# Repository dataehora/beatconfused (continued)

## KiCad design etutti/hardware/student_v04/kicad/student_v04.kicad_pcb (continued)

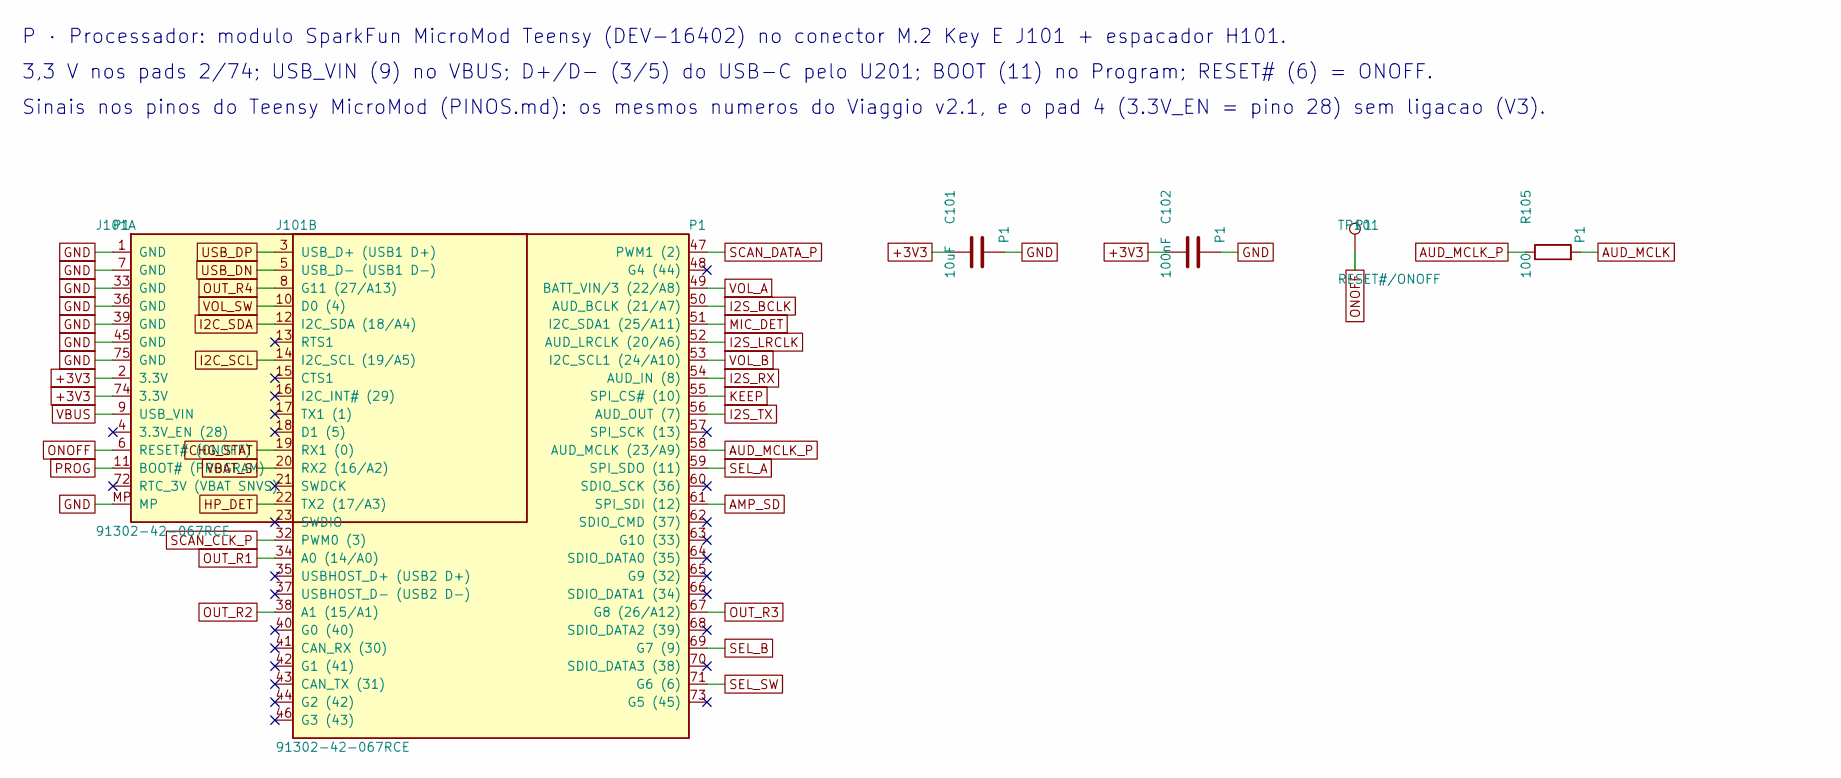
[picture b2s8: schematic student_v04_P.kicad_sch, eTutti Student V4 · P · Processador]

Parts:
C101: 10uF; C_0805_2012Metric; LCSC C15850
C102: 100nF; C_0402_1005Metric; LCSC C1525
J101: 91302-42-067RCE; M.2_E_H4.2_UMAX_91302-42-067; LCSC C48985906
R105: 100; R_0402_1005Metric; LCSC C25076
TP101: RESET#/ONOFF; TestPoint_Pad_D1.5mm

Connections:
+3V3: C101.1, C102.1, J101.2 (3.3V), J101.74 (3.3V); also elsewhere on the board
AMP_SD: J101.61 (SPI_SDI (12)); also elsewhere on the board
AUD_MCLK: R105.2; also elsewhere on the board
AUD_MCLK_P: J101.58 (AUD_MCLK (23/A9)), R105.1
CHG_STAT: J101.19 (RX1 (0)); also elsewhere on the board
GND: C101.2, C102.2, J101.1 (GND), J101.7 (GND), J101.33 (GND), J101.36 (GND), J101.39 (GND), J101.45 (GND), J101.75 (GND), J101.MP; also elsewhere on the board
HP_DET: J101.22 (TX2 (17/A3)); also elsewhere on the board
I2C_SCL: J101.14 (I2C_SCL (19/A5)); also elsewhere on the board
I2C_SDA: J101.12 (I2C_SDA (18/A4)); also elsewhere on the board
I2S_BCLK: J101.50 (AUD_BCLK (21/A7)); also elsewhere on the board
I2S_LRCLK: J101.52 (AUD_LRCLK (20/A6)); also elsewhere on the board
I2S_RX: J101.54 (AUD_IN (8)); also elsewhere on the board
I2S_TX: J101.56 (AUD_OUT (7)); also elsewhere on the board
KEEP: J101.55 (SPI_CS# (10)); also elsewhere on the board
MIC_DET: J101.51 (I2C_SDA1 (25/A11)); also elsewhere on the board
ONOFF: J101.6 (RESET# (ONOFF)), TP101.1; also elsewhere on the board
OUT_R1: J101.34 (A0 (14/A0)); also elsewhere on the board
OUT_R2: J101.38 (A1 (15/A1)); also elsewhere on the board
OUT_R3: J101.67 (G8 (26/A12)); also elsewhere on the board
OUT_R4: J101.8 (G11 (27/A13)); also elsewhere on the board
PROG: J101.11 (BOOT# (PROGRAM)); also elsewhere on the board
SCAN_CLK_P: J101.32 (PWM0 (3)); also elsewhere on the board
SCAN_DATA_P: J101.47 (PWM1 (2)); also elsewhere on the board
SEL_A: J101.59 (SPI_SDO (11)); also elsewhere on the board
SEL_B: J101.69 (G7 (9)); also elsewhere on the board
SEL_SW: J101.71 (G6 (6)); also elsewhere on the board
USB_DN: J101.5 (USB_D- (USB1 D-)); also elsewhere on the board
USB_DP: J101.3 (USB_D+ (USB1 D+)); also elsewhere on the board
VBAT_S: J101.20 (RX2 (16/A2)); also elsewhere on the board
VBUS: J101.9 (USB_VIN); also elsewhere on the board
VOL_A: J101.49 (BATT_VIN/3 (22/A8)); also elsewhere on the board
VOL_B: J101.53 (I2C_SCL1 (24/A10)); also elsewhere on the board
VOL_SW: J101.10 (D0 (4)); also elsewhere on the board

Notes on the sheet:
P · Processador: modulo SparkFun MicroMod Teensy (DEV-16402) no conector M.2 Key E J101 + espacador H101.
3,3 V nos pads 2/74; USB_VIN (9) no VBUS; D+/D- (3/5) do USB-C pelo U201; BOOT (11) no Program; RESET# (6) = ONOFF.
Sinais nos pinos do Teensy MicroMod (PINOS.md): os mesmos numeros do Viaggio v2.1, e o pad 4 (3.3V_EN = pino 28) sem ligacao (V3).

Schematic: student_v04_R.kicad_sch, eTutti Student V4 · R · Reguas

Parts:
J601, J602, J603, J604: SM06B-SRSS-TB(LF)(SN); JST_SH_SM06B-SRSS-TB_1x06-1MP_P1.00mm_Horizontal; LCSC C160405
R601, R602, R603, R604: 100k; R_0402_1005Metric; LCSC C25741
R605, R606: 330; R_0402_1005Metric; LCSC C25104

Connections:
+3V3: J601.1, J602.1, J603.1, J604.1; also elsewhere on the board
GND: J601.2, J601.4, J601.MP (MountPin), J602.2, J602.4, J602.MP (MountPin), J603.2, J603.4, J603.MP (MountPin), J604.2, J604.4, J604.MP (MountPin), R601.2, R602.2, R603.2, R604.2; also elsewhere on the board
OUT_R1: J601.3, R601.1; also elsewhere on the board
OUT_R2: J602.3, R602.1; also elsewhere on the board
OUT_R3: J603.3, R603.1; also elsewhere on the board
OUT_R4: J604.3, R604.1; also elsewhere on the board
SCAN_CLK: J601.5, J602.5, J603.5, J604.5, R605.2
SCAN_CLK_P: R605.1; also elsewhere on the board
SCAN_DATA: J601.6, J602.6, J603.6, J604.6, R606.2
SCAN_DATA_P: R606.1; also elsewhere on the board

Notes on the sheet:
R · Reguas: 4 conectores SH de 6 vias (um por fileira) levam +3V3, GND, OUT_Rk, CLK e DATA aos 74HC595 + 4 TMAG5253 de cada regua.
OUT_Rk: pull-down de 100 k na placa principal; CLK e DATA comuns as 4 fileiras, por 330 ohm (R8V4, pinagem P6s). Sem sensores nem multiplexadores aqui.

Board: 4 copper layers, 88 parts (80 on the bottom side), 64 nets, no tracks yet.

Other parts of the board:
H1, H2, H3, H4: MountingHole_2.2mm_M2
H101: MountingHole_2.7mm_M2.5

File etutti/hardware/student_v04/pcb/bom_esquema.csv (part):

codigo,referencias,qtd,valor_peca,encapsulamento,lcsc,classe_jlc,preco_unit_usd_est,montagem,status,nota
I3,DS1,1,"Adafruit 326: OLED 0,96 pol. monocromatico 128 x 64, SSD1306, 2 conectores STEMMA QT (SH 4 vias), regulador de bordo AP2112K-3.3","29,2 x 26,7 mm (+ orelhas, 31,75 de comprimento) (conferir)",-,-,17.500,em casa (preso na tampa; cabo Qwiic ao J401),conferir,"R11V4: 4 furos; endereco I2C 0x3D de fabrica (0x3C por jumper); US$ 17,50 (1-9), 15,75 (10-99)"
I3,CAB1,1,"cabo Qwiic / STEMMA QT (SH 1,0 mm, 4 vias, pino a pino), 50 mm (Adafruit 4210 ou SparkFun)",-,-,-,1.000,em casa,final,
P1,MOD1,1,SparkFun MicroMod Teensy Processor (DEV-16402),M.2 2222 Key E,-,-,24.950,"em casa (encaixar no J101, apertar o parafuso)",final,"i.MX RT1062 600 MHz, 16 MB flash, 1 MB RAM, bootloader MKL02; fqbn teensy:avr:teensyMM"
P1,SCR1,1,"parafuso M2.5 x 3, cabeca chata (Phillips)",-,-,-,0.050,em casa,conferir,prende o modulo no espacador H101 (vem no KIT-16549 da SparkFun)
P1,R105,1,100,R_0402_1005Metric,C25076,basica,0.001,JLC,final,"MCLK 11,3 MHz: em serie, junto do J101 (SPEC 4, 5o)"
P1,C102,1,100nF,C_0402_1005Metric,C1525,basica,0.001,JLC,final,
P1,C101,1,10uF,C_0805_2012Metric,C15850,basica,0.008,JLC,final,"3,3 V junto dos pads 2/74 do J101"
P1,J101,1,91302-42-067RCE,M.2_E_H4.2_UMAX_91302-42-067,C48985906,estendida,1.260,JLC,conferir,"UMAX M.2 Key E 67 pinos, 0,5 mm, 4,2 mm (estoque LCSC 622 em 25 out 2026; o LOTES C841659 estava com 0); footprint pelo desenho UMAX C-91302-42 rev C; no verso; modulo SparkFun MicroMod Teensy DEV-16402 encaixado em casa"
P1,TP101,1,RESET#/ONOFF,TestPoint_Pad_D1.5mm,-,-,0.000,sem peca (pad),final,pad 6 do MicroMod = ONOFF do RT1062 no modulo Teensy (nao e o POR_B); ver ELETRONICA.md
E1,R201 R202,2,5.1k,R_0402_1005Metric,C25905,basica,0.001,JLC,final,
E1,J201,1,TYPE-C-31-M-12,USB_C_Receptacle_HRO_TYPE-C-31-M-12,C165948,estendida,0.150,JLC,final,"lado de cima, borda esquerda, boca para fora"
E2,D201,1,SMF5.0A,D_SOD-123F,C151296,estendida,0.050,JLC,final,"TVS do VBUS (Pocket D60); lado de cima, junto do USB-C (SPEC v2.3)"
E2,U201,1,USBLC6-2SC6,SOT-23-6,C7519,basica,0.050,JLC,conferir,"lado de cima, junto do USB-C (SPEC v2.3)"
E3,R204,1,1.5k,R_0402_1005Metric,C25867,basica,0.001,JLC,conferir,"so vale com EN2=1 (1,07 A); obrigatorio"
E3,R206 R210 R211 R213 R215,5,100k,R_0402_1005Metric,C25741,basica,0.001,JLC,final,
E3,C204 C205,2,100nF,C_0402_1005Metric,C1525,basica,0.001,JLC,final,
E3,R205 R214,2,10k,R_0402_1005Metric,C25744,basica,0.001,JLC,final,
E3,C201 C202 C203,3,10uF,C_0805_2012Metric,C15850,basica,0.008,JLC,final,
E3,C210,1,10uF,C_0603_1608Metric,C19702,basica,0.005,JLC,final,"VSYS junto dos pinos OUT (10/11) do U202, no lado de cima (M3)"
E3,R208 R209 R212,3,1M,R_0402_1005Metric,C26083,basica,0.001,JLC,final,medida da bateria: V(pino 16) = VBAT/2
E3,R203,1,2.2k,R_0402_1005Metric,C25879,basica,0.001,JLC,conferir,"ICHG = 890/2200 = 0,405 A (K_ISET do datasheet)"
E3,Q203,1,AO3401A,SOT-23,C15127,basica,0.010,JLC,final,o clique do volume liga o EN
E3,D202 D203 D205 D206,4,BAV70,SOT-23,C68978,basica,0.020,JLC,final,"leitura do ~CHG pelo pino 0 (so com USB; R3V4: saiu do 26, que virou OUT_R3)"
E3,U202,1,BQ24074RGTR,VQFN-16-1EP_3x3mm_P0.5mm_EP1.6x1.6mm,C54313,estendida,1.100,JLC,final,"USB500 (EN2=0, EN1=1), 500 mA, NTC no TS; TMR e ITERM abertos = padrao; OUT 4,4 V com USB"
E4,R216,1,100,R_0402_1005Metric,C25076,basica,0.001,JLC,final,
E4,C209,1,100nF,C_0402_1005Metric,C1525,basica,0.001,JLC,final,
E4,C206 C207 C208,3,10uF,C_0805_2012Metric,C15850,basica,0.008,JLC,final,
E4,L201,1,2.2uH,L_Changjiang_FNR4020S,C167825,estendida,0.080,JLC,final,FNR4020S2R2MT (Pocket L10)
E4,U204,1,TPS63001DRCR,Texas_DRC0010J,C28060,estendida,1.400,JLC,final,"3,3 V fixo; PS/SYNC baixo = economia; EN = EN_REQ (sem a porta U206 da v2.1)"
E6,J202,1,S3B-PH-SM4-TB,JST_PH_S3B-PH-SM4-TB_1x03-1MP_P2.00mm_Horizontal,C265101,estendida,0.300,JLC,final,"bateria 1 = +, 2 = NTC, 3 = - (ordem do Pocket; conferir o cabo)"
F1,C302 C304 C305 C307,4,100nF,C_0402_1005Metric,C1525,basica,0.001,JLC,final,
F1,R301 R302,2,2.2k,R_0402_1005Metric,C25879,basica,0.001,JLC,conferir,
F1,C301 C303 C306,3,2.2uF,C_0402_1005Metric,C12530,basica,0.003,JLC,conferir,
F1,FB301,1,600R@100MHz,L_0603_1608Metric,C1002,basica,0.005,JLC,final,Audio Board: Ferrite 600 no VDDA
F1,U301,1,SGTL5000XNLA3,QFN-20-1EP_3x3mm_P0.4mm_EP1.65x1.65mm,C2651833,estendida,1.800,JLC,conferir,"como a Audio Board Rev D2 (endereco I2C fixo 0x0A); V2: entrada de microfone (MIC, MIC_BIAS) e I2S_DOUT ligados"
F1,U302,1,XC6206P182MR,SOT-23-3,C347373,estendida,0.030,JLC,conferir,"1,8 V do VDDD (a Audio Board usa AP7313)"
F2,R303,1,100k,R_0402_1005Metric,C25741,basica,0.001,JLC,final,
F2,C308,1,100nF,C_0402_1005Metric,C1525,basica,0.001,JLC,final,
F2,R304,1,1M,R_0402_1005Metric,C26083,basica,0.001,JLC,final,
F2,J301,1,PJ-327A,Jack_3.5mm_PJ-327A_SMD,C49284723,estendida,0.100,JLC,conferir,"SMD, angulo reto, XUNPU (V3; o SHOU HAN 5JJ foi trocado porque a JLCPCB o marca como dificil de montar); 2/5 manga (HP_VGND, nunca no GND), 6 anel, 4 ponta, 3 contato da ponta (fechado sem plugue)"
F3,R305,1,0,R_0402_1005Metric,C17168,basica,0.001,JLC,final,"R8V4: 0 ohm (aprovado): bias total = 2 k internos do SGTL5000 (BIAS_RESISTOR 2k); era 2,2 k em serie (4,2 k). Mais tensao para microfones que pedem mais"
F3,R306,1,100k,R_0402_1005Metric,C25741,basica,0.001,JLC,final,R6V4: toma de CC da ponta do IN para o ADC (pino 25): distingue microfone de eletreto de plugue de linha/sem plugue
F3,C311,1,100nF,C_0402_1005Metric,C1525,basica,0.001,JLC,final,R6V4: filtro da toma MIC_DET (RC 10 ms; o ADC lê devagar)
F3,C310,1,100nF,C_0402_1005Metric,C1525,basica,0.001,nao montar,final,"R10V4: NAO MONTAR. Datasheet SGTL5000 Fig. 20 poe 0,1 uF no MIC_BIAS (C4) COM o R1 de 2,2 k em serie; com R305 = 0 ohm o C310 fica na ponta do jack e forma um passa-baixas com os 2 k do bias (~800 Hz, -14 dB a 4 kHz). Pad mantido para um 220-470 pF opcional se a bancada mostrar ruido do bias"
F3,C309,1,1uF,C_0402_1005Metric,C52923,basica,0.002,JLC,final,"acoplamento do microfone ao pino MIC (o datasheet mostra 0,1 uF; 1 uF baixa o corte da voz)"
F3,J302,1,PJ-327A,Jack_3.5mm_PJ-327A_SMD,C49284723,estendida,0.100,JLC,final,"IN (microfone): manga no GND, ponta = sinal com bias; anel e contato da ponta soltos (XUNPU, V3)"
I1,SW401,1,EC11E18244AU,RotaryEncoder_Alps_EC11E-Switch_Vertical_H20mm,C202365,estendida,1.920,"sem peca (encoder soldado em casa, topo)",final,volume; clique de 2 s liga/desliga; eixo de 20 mm (o knob chapeu tem 7 mm); 18 pulsos / 36 detentes: ENC_STEPS_PER_DETENT = 2
I2,SW402,1,EC11E18244AU,RotaryEncoder_Alps_EC11E-Switch_Vertical_H20mm,C202365,estendida,1.920,"sem peca (encoder soldado em casa, topo)",final,seletor; clique = funcoes de som; eixo de 20 mm (o knob chapeu tem 7 mm); 18 pulsos / 36 detentes: ENC_STEPS_PER_DETENT = 2
I3,J401,1,SM04B-SRSS-TB(LF)(SN),JST_SH_SM04B-SRSS-TB_1x04-1MP_P1.00mm_Horizontal,C160404,estendida,0.215,JLC,conferir,"R11V4: tela OLED Adafruit 326 (0,96 pol., SSD1306, 128 x 64, STEMMA QT) por um cabo Qwiic / STEMMA QT de estoque (SH de 4 vias nas duas pontas, pino a pino): ordem Qwiic 1 GND, 2 +3V3, 3 SDA, 4 SCL. Era um SH de 6 vias (o mesmo das reguas, ordem 1 +3V3) que obrigava a um cabo 6-4 sob medida; o tipo Extended a mais custa US$ 3,09 por pedido e economiza o cabo sob medida. Clone SM04B-SRSS-TB(LF)(SN) (C160404, 17958 em estoque); original JST C160404"
I4,SW403,1,Program,SW_Push_1P1T_XKB_TS-1187A,C318884,basica,0.020,JLC,conferir,"no verso, por um furo no fundo; 5,1 x 5,1 (a SPEC pedia 4 x 4)"
A1,C502,1,100nF,C_0402_1005Metric,C1525,basica,0.001,JLC,final,
A1,C501,1,10uF,C_0805_2012Metric,C15850,basica,0.008,JLC,final,
A1,R501,1,1M,R_0402_1005Metric,C26083,basica,0.001,JLC,final,"com os 100k internos: 0,30 V no SD_MODE (janela mono 0,16-0,77 V); pino baixo = desligado"
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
